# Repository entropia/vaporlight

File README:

Vaporlight
==========

The Vaporlight is Entropias LED lighting system.

More documentation (including pictures) is available
at https://entropia.de/Vaporlight.

Where to find what
------------------

/HACKING                       Describes some internals
/hardware                      Schematics and PCB layouts (Eagle)
/vaporware/led-boards          Firmware for the LED modules (C)
/config                        OpenOCD config files
/vaporware/emulator            Hardware emulator (Python)
/vaporware/daemon              TCP <-> Bus router (Scala)
/vaporware/language_bindings   Libraries for talking to the router (Python, C++)
/misc                          z.B. Schutzecken zum 3D-Drucken (OpenSCAD)

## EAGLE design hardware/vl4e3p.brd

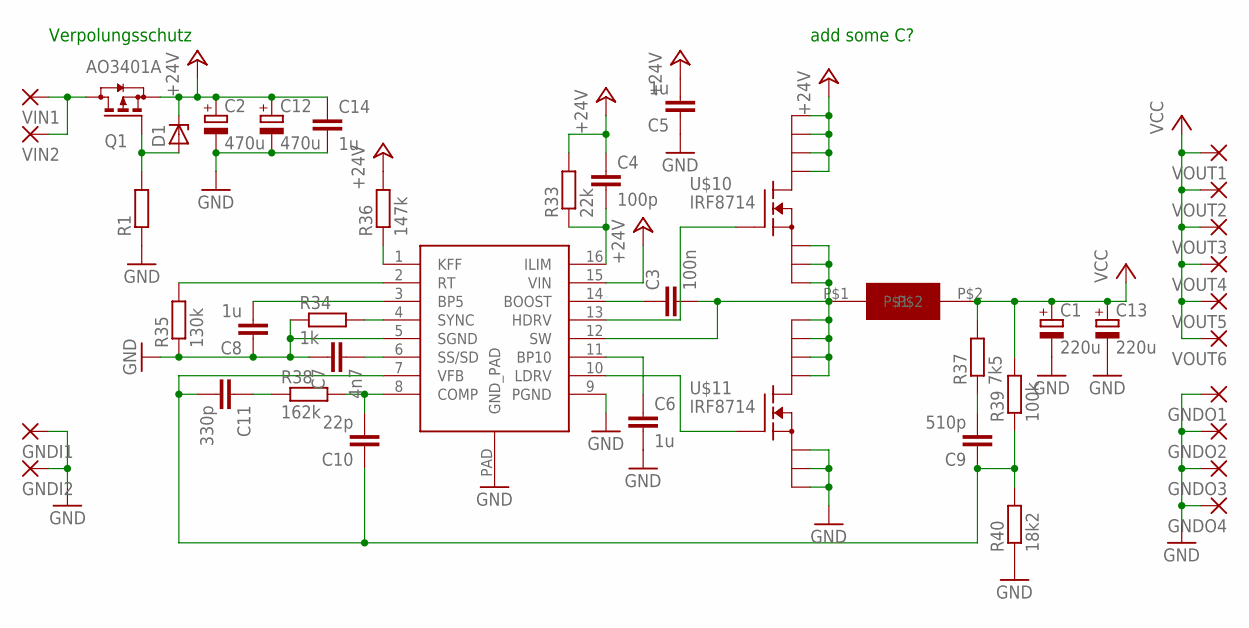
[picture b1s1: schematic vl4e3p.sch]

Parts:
C1, C13: 220u; E3,5-8
C2, C12: 470u; E3,5-8
C3: 100n; C0805S
C4: 100p; C0805
C5, C6, C8, C14: 1u; C0805
C7: 4n7; C0805
C9: 510p; C0805
C10: 22p; C0805
C11: 330p; C0805
D1: ZENER-DIODESOT23; SOT23
GNDI1, GNDI2: PAD5-2,5; 5-2,5
GNDO1, GNDO2, GNDO3, GNDO4: PAD5-2,5; 5-2,5
Q1: AO3401A; SOT23
R1: R-EU_R0805; R0805
R33: 22k; R0805
R34: 1k; R0805
R35: 130k; R0805
R36: 147k; R0805
R37: 7k5; R0805
R38: 162k; R0805
R39: 100k; R0805
R40: 18k2; R0805
U$1: 6u8; FOO
U$9: TPS40055; TSSOP16
U$10, U$11: IRF8714; SO8
VIN1, VIN2: PAD5-2,5; 5-2,5
VOUT1, VOUT2, VOUT3, VOUT4, VOUT5, VOUT6: PAD5-2,5; 5-2,5

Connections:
+24V: C2.+, C4.1, C5.2, C12.+, C14.1, D1.3 (C), Q1.2 (S), R33.2, R36.2, U$9.15 (VIN), U$10.5 (D), U$10.6 (D), U$10.7 (D), U$10.8 (D)
BOOST: C3.1, U$9.14 (BOOST)
BP10: C6.1, U$9.11 (BP10)
C3: C8.2, U$9.3 (BP5)
COMP: C10.2, R38.2, U$9.8 (COMP)
GND: C1.-, C2.-, C5.1, C6.2, C7.1, C8.1, C12.-, C13.-, C14.2, GNDI1.1, GNDI2.1, GNDO1.1, GNDO2.1, GNDO3.1, GNDO4.1, R1.1, R34.1, R35.1, R40.1, U$9.5 (SGND), U$9.9 (PGND), U$9.PAD (GND_PAD), U$11.1 (S), U$11.2 (S), U$11.3 (S)
HDRV: U$9.13 (HDRV), U$10.4 (G)
ILIM: C4.2, R33.1, U$9.16 (ILIM)
KFF: R36.1, U$9.1 (KFF)
LDRV: U$9.10 (LDRV), U$11.4 (G)
unnamed: C11.1, R38.1
unnamed: C9.2, R37.1
unnamed: D1.1 (A), Q1.1 (G), R1.2
RT: R35.2, U$9.2 (RT)
SS/SD: C7.2, U$9.6 (SS/SD)
SW: C3.2, U$1.P$1, U$9.12 (SW), U$10.1 (S), U$10.2 (S), U$10.3 (S), U$11.5 (D), U$11.6 (D), U$11.7 (D), U$11.8 (D)
SYNC: R34.2, U$9.4 (SYNC)
VCC: C1.+, C13.+, R37.2, R39.2, U$1.P$2, VOUT1.1, VOUT2.1, VOUT3.1, VOUT4.1, VOUT5.1, VOUT6.1
VFB: C9.1, C10.1, C11.2, R39.1, R40.2, U$9.7 (VFB)
VIN: Q1.3 (D), VIN1.1, VIN2.1

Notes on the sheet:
Verpolungsschutz
add some C?

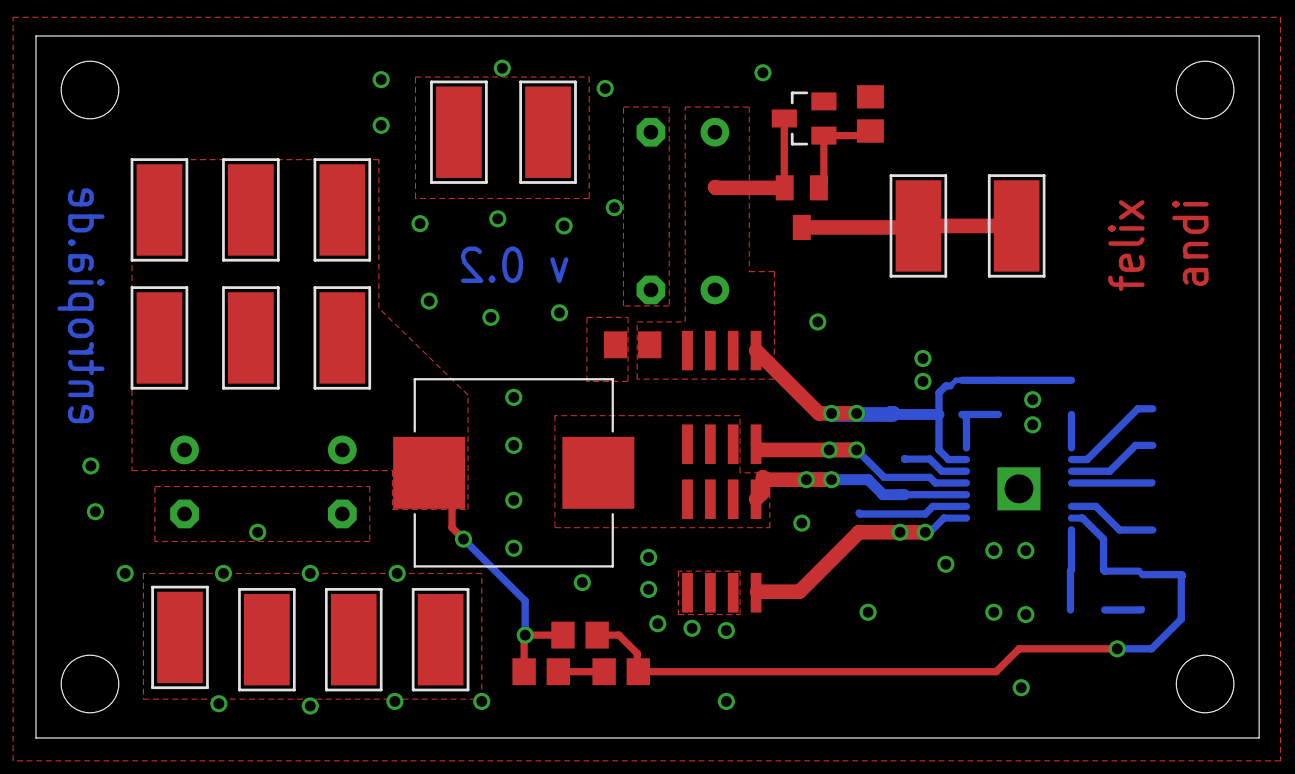
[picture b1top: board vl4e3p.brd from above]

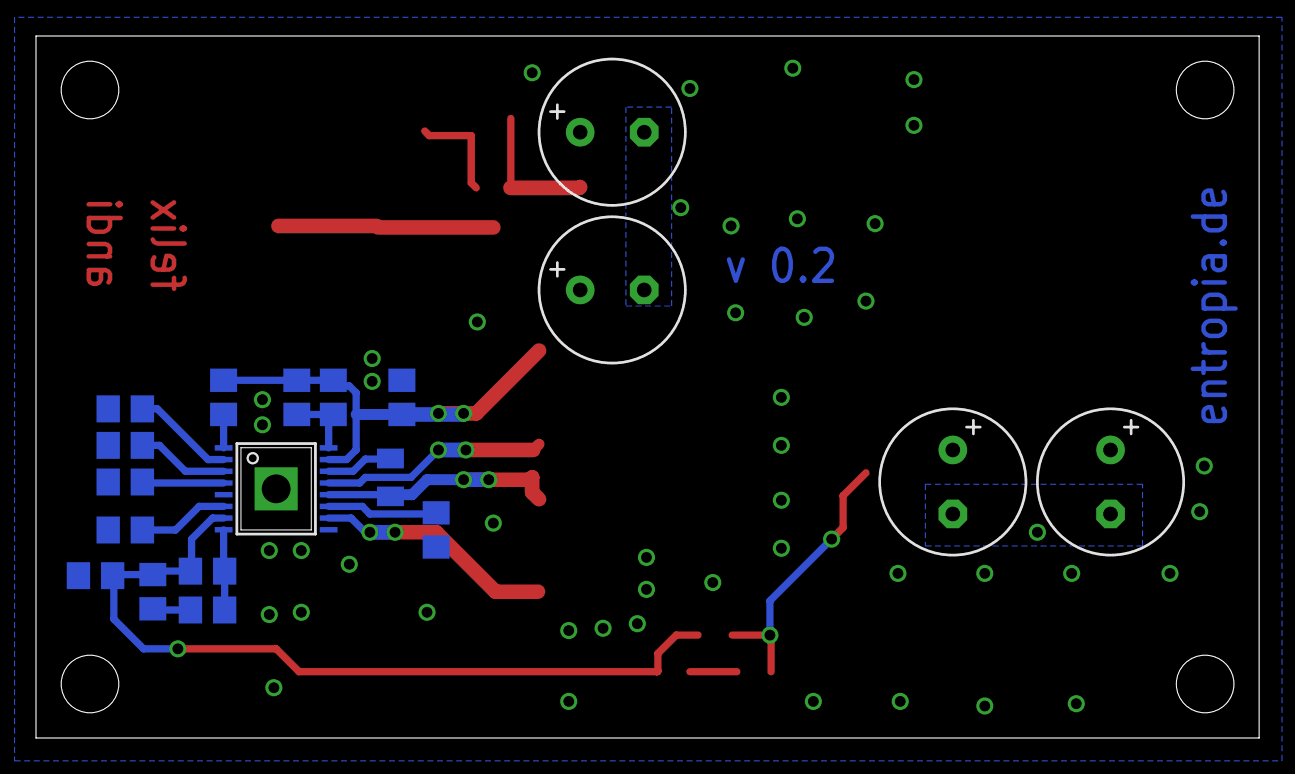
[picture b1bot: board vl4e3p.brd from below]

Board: 2 copper layers, 68.0 x 39.0 mm, 43 parts (19 on the bottom side), 20 nets.

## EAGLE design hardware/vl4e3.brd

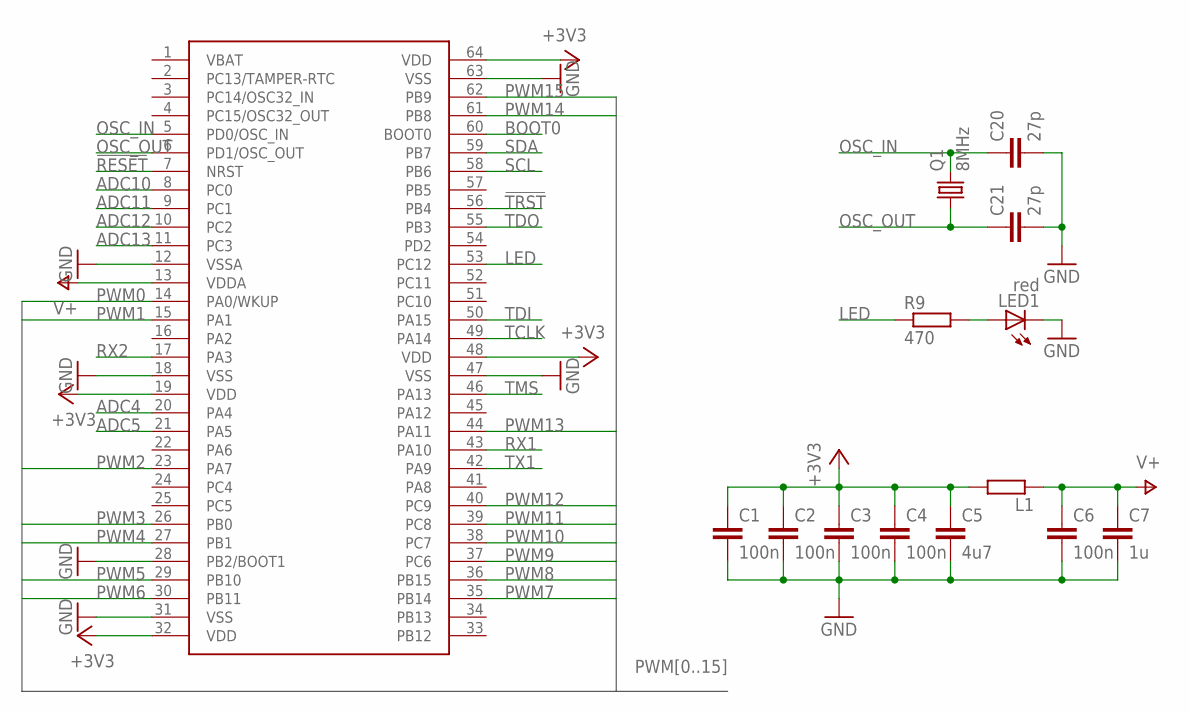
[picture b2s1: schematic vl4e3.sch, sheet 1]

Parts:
C1, C2, C3, C4, C6: 100n; C0603
C5: 4u7; C0805
C7: 1u; C0805
C20, C21: 27p; C0603
L1: R-EU_R0805; R0805
LED1: red; CHIPLED_0805
Q1: 8MHz; HC49/S
R9: 470; R0805
U$1: STM32F100R; TQFP64-10X10

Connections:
!RESET: U$1.7 (NRST); also elsewhere on the board
!TRST: U$1.56 (PB4); also elsewhere on the board
+3V3: C1.1, C2.1, C3.1, C4.1, C5.1, L1.2, U$1.19 (VDD), U$1.32 (VDD), U$1.48 (VDD), U$1.64 (VDD); also elsewhere on the board
ADC4: U$1.20 (PA4); also elsewhere on the board
ADC5: U$1.21 (PA5); also elsewhere on the board
ADC10: U$1.8 (PC0); also elsewhere on the board
ADC11: U$1.9 (PC1); also elsewhere on the board
ADC12: U$1.10 (PC2); also elsewhere on the board
ADC13: U$1.11 (PC3); also elsewhere on the board
BOOT0: U$1.60 (BOOT0); also elsewhere on the board
GND: C1.2, C2.2, C3.2, C4.2, C5.2, C6.2, C7.2, C20.2, C21.2, LED1.C, U$1.12 (VSSA), U$1.18 (VSS), U$1.28 (PB2/BOOT1), U$1.31 (VSS), U$1.47 (VSS), U$1.63 (VSS); also elsewhere on the board
LED: R9.1, U$1.53 (PC12)
LED_R: LED1.A, R9.2
OSC_IN: C20.1, Q1.2, U$1.5 (PD0/OSC_IN)
OSC_OUT: C21.1, Q1.1, U$1.6 (PD1/OSC_OUT)
PWM0: U$1.14 (PA0/WKUP); also elsewhere on the board
PWM1: U$1.15 (PA1); also elsewhere on the board
PWM2: U$1.23 (PA7); also elsewhere on the board
PWM3: U$1.26 (PB0); also elsewhere on the board
PWM4: U$1.27 (PB1); also elsewhere on the board
PWM5: U$1.29 (PB10); also elsewhere on the board
PWM6: U$1.30 (PB11); also elsewhere on the board
PWM7: U$1.35 (PB14); also elsewhere on the board
PWM8: U$1.36 (PB15); also elsewhere on the board
PWM9: U$1.37 (PC6); also elsewhere on the board
PWM10: U$1.38 (PC7); also elsewhere on the board
PWM11: U$1.39 (PC8); also elsewhere on the board
PWM12: U$1.40 (PC9); also elsewhere on the board
PWM13: U$1.44 (PA11); also elsewhere on the board
PWM14: U$1.61 (PB8); also elsewhere on the board
PWM15: U$1.62 (PB9); also elsewhere on the board
RX1: U$1.43 (PA10); also elsewhere on the board
RX2: U$1.17 (PA3); also elsewhere on the board
SCL: U$1.58 (PB6)
SDA: U$1.59 (PB7)
TCLK: U$1.49 (PA14); also elsewhere on the board
TDI: U$1.50 (PA15); also elsewhere on the board
TDO: U$1.55 (PB3); also elsewhere on the board
TMS: U$1.46 (PA13); also elsewhere on the board
TX1: U$1.42 (PA9); also elsewhere on the board
V+: C6.1, C7.1, L1.1, U$1.13 (VDDA)

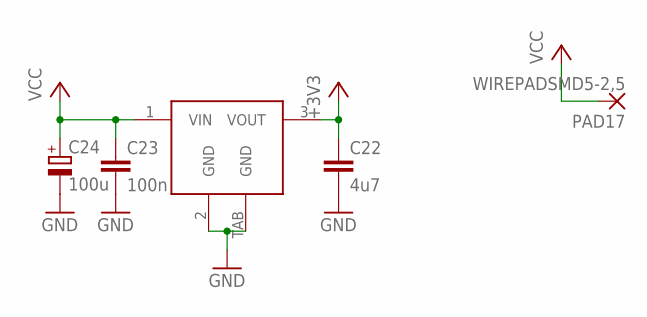
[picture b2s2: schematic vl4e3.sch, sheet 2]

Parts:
C22: 4u7; C0805
C23: 100n; C0603
C24: 100u; E2,5-6
PAD17: WIREPADSMD5-2,5; 5-2,5
U$10: MIC5209; SOT223

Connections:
+3V3: C22.1, U$10.3 (VOUT); also elsewhere on the board
GND: C22.2, C23.2, C24.-, U$10.2 (GND), U$10.TAB (GND); also elsewhere on the board
VCC: C23.1, C24.+, PAD17.1, U$10.1 (VIN); also elsewhere on the board

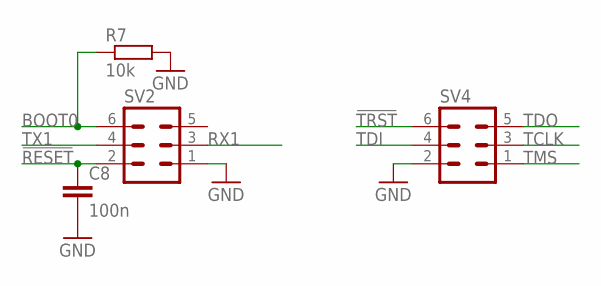
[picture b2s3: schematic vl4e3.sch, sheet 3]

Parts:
C8: 100n; C0603
R7: 10k; R0603
SV2, SV4: MA03-2

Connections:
!RESET: C8.1, SV2.2; also elsewhere on the board
!TRST: SV4.6; also elsewhere on the board
BOOT0: R7.1, SV2.6; also elsewhere on the board
GND: C8.2, R7.2, SV2.1, SV4.2; also elsewhere on the board
RX1: SV2.3; also elsewhere on the board
TCLK: SV4.3; also elsewhere on the board
TDI: SV4.4; also elsewhere on the board
TDO: SV4.5; also elsewhere on the board
TMS: SV4.1; also elsewhere on the board
TX1: SV2.4; also elsewhere on the board

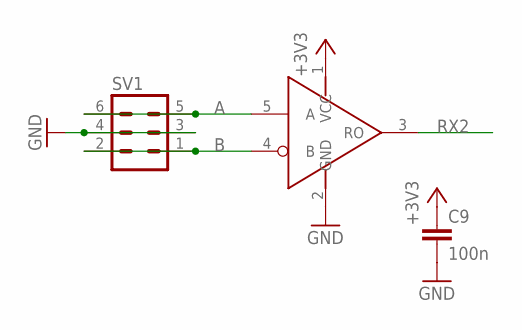
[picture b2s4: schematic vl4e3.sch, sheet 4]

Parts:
C9: 100n; C0603
SV1: MA03-2
U$13: ISL3280E; SOT23-5L

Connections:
+3V3: C9.1, U$13.1 (VCC); also elsewhere on the board
A: SV1.5, SV1.6, U$13.5 (A)
B: SV1.1, SV1.2, U$13.4 (B)
GND: C9.2, SV1.3, SV1.4, U$13.2 (GND); also elsewhere on the board
RX2: U$13.3 (RO); also elsewhere on the board

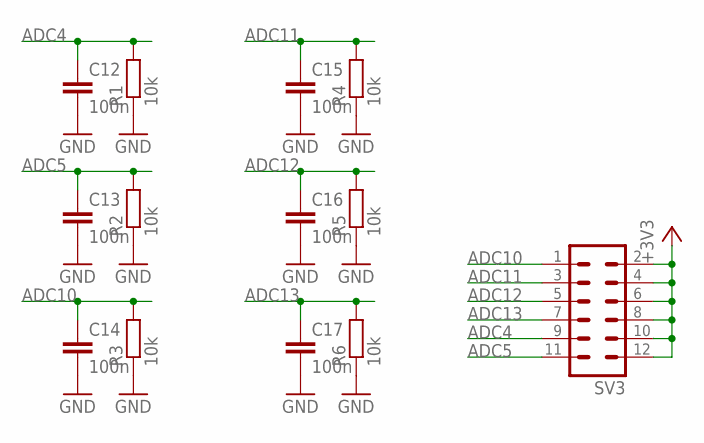
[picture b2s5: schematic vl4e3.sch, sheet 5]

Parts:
C12, C13, C14, C15, C16, C17: 100n; C0603
R1, R2, R3, R4, R5, R6: 10k; R0603
SV3: MA06-2

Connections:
+3V3: SV3.2, SV3.4, SV3.6, SV3.8, SV3.10, SV3.12; also elsewhere on the board
ADC4: C12.1, R1.2, SV3.9; also elsewhere on the board
ADC5: C13.1, R2.2, SV3.11; also elsewhere on the board
ADC10: C14.1, R3.2, SV3.1; also elsewhere on the board
ADC11: C15.1, R4.2, SV3.3; also elsewhere on the board
ADC12: C16.1, R5.2, SV3.5; also elsewhere on the board
ADC13: C17.1, R6.2, SV3.7; also elsewhere on the board
GND: C12.2, C13.2, C14.2, C15.2, C16.2, C17.2, R1.1, R2.1, R3.1, R4.1, R5.1, R6.1; also elsewhere on the board

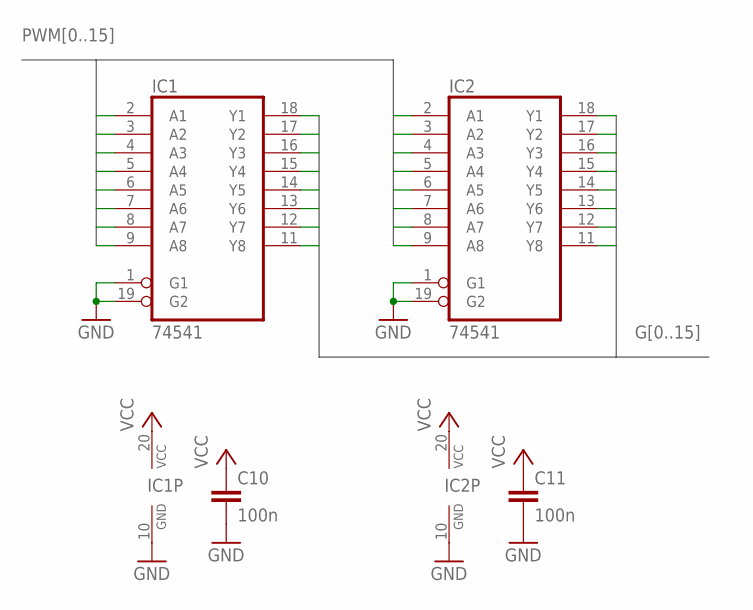
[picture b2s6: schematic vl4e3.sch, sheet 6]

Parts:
C10, C11: 100n; C0603
IC1, IC2: 74541; TSSOP20

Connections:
G0: IC1.18 (Y1); also elsewhere on the board
G1: IC1.17 (Y2); also elsewhere on the board
G2: IC1.16 (Y3); also elsewhere on the board
G3: IC1.15 (Y4); also elsewhere on the board
G4: IC1.14 (Y5); also elsewhere on the board
G5: IC1.13 (Y6); also elsewhere on the board
G6: IC1.12 (Y7); also elsewhere on the board
G7: IC1.11 (Y8); also elsewhere on the board
G8: IC2.18 (Y1); also elsewhere on the board
G9: IC2.17 (Y2); also elsewhere on the board
G10: IC2.16 (Y3); also elsewhere on the board
G11: IC2.15 (Y4); also elsewhere on the board
G12: IC2.14 (Y5); also elsewhere on the board
G13: IC2.13 (Y6); also elsewhere on the board
G14: IC2.12 (Y7); also elsewhere on the board
G15: IC2.11 (Y8); also elsewhere on the board
GND: C10.2, C11.2, IC1.1 (G1), IC1.10 (GND), IC1.19 (G2), IC2.1 (G1), IC2.10 (GND), IC2.19 (G2); also elsewhere on the board
PWM0: IC1.2 (A1); also elsewhere on the board
PWM1: IC1.3 (A2); also elsewhere on the board
PWM2: IC1.4 (A3); also elsewhere on the board
PWM3: IC1.5 (A4); also elsewhere on the board
PWM4: IC1.6 (A5); also elsewhere on the board
PWM5: IC1.7 (A6); also elsewhere on the board
PWM6: IC1.8 (A7); also elsewhere on the board
PWM7: IC1.9 (A8); also elsewhere on the board
PWM8: IC2.2 (A1); also elsewhere on the board
PWM9: IC2.3 (A2); also elsewhere on the board
PWM10: IC2.4 (A3); also elsewhere on the board
PWM11: IC2.5 (A4); also elsewhere on the board
PWM12: IC2.6 (A5); also elsewhere on the board
PWM13: IC2.7 (A6); also elsewhere on the board
PWM14: IC2.8 (A7); also elsewhere on the board
PWM15: IC2.9 (A8); also elsewhere on the board
VCC: C10.1, C11.1, IC1.20 (VCC), IC2.20 (VCC); also elsewhere on the board

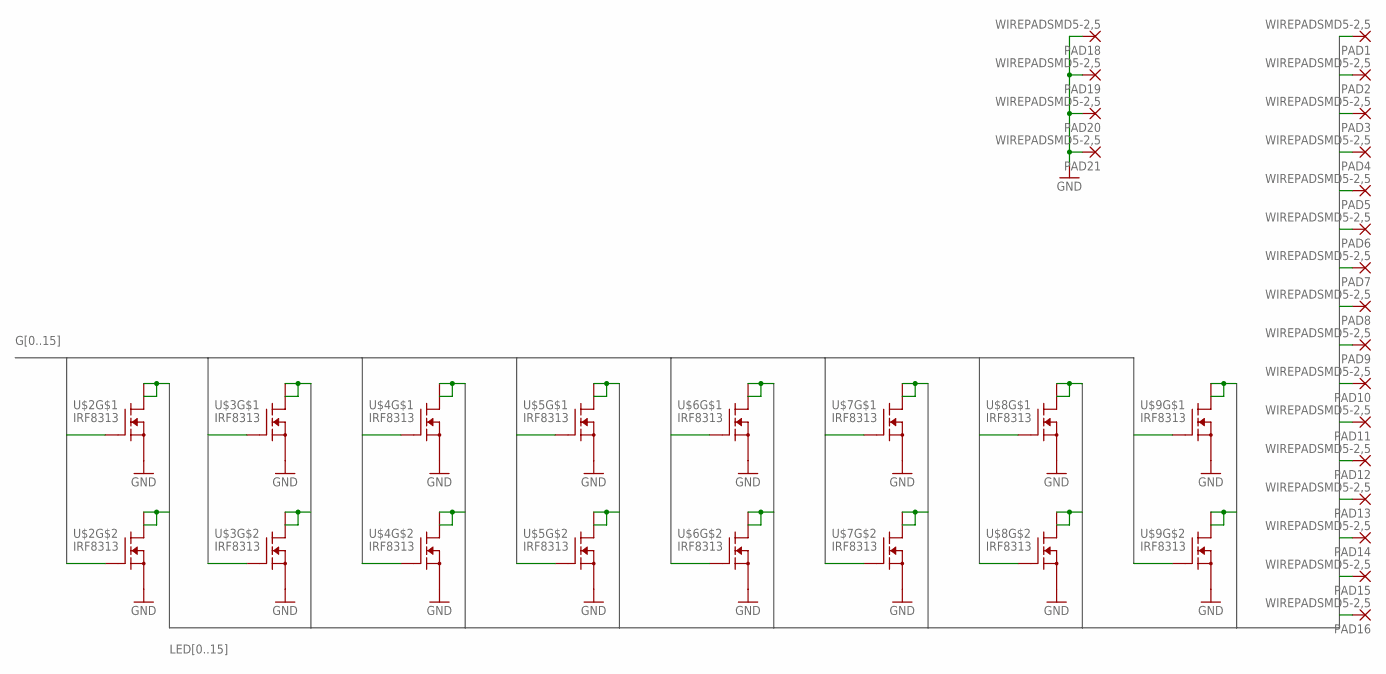
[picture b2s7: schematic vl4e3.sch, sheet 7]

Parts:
PAD1, PAD2, PAD3, PAD4, PAD5, PAD6, PAD7, PAD8, PAD9, PAD10, PAD11, PAD12, PAD13, PAD14, PAD15, PAD16, PAD18, PAD19, PAD20, PAD21: WIREPADSMD5-2,5; 5-2,5
U$2, U$3, U$4, U$5, U$6, U$7, U$8, U$9: IRF8313; SO-08

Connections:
G0: U$2.2 (G); also elsewhere on the board
G1: U$2.4 (G); also elsewhere on the board
G2: U$3.2 (G); also elsewhere on the board
G3: U$3.4 (G); also elsewhere on the board
G4: U$4.2 (G); also elsewhere on the board
G5: U$4.4 (G); also elsewhere on the board
G6: U$5.2 (G); also elsewhere on the board
G7: U$5.4 (G); also elsewhere on the board
G8: U$6.2 (G); also elsewhere on the board
G9: U$6.4 (G); also elsewhere on the board
G10: U$7.2 (G); also elsewhere on the board
G11: U$7.4 (G); also elsewhere on the board
G12: U$8.2 (G); also elsewhere on the board
G13: U$8.4 (G); also elsewhere on the board
G14: U$9.2 (G); also elsewhere on the board
G15: U$9.4 (G); also elsewhere on the board
GND: PAD18.1, PAD19.1, PAD20.1, PAD21.1, U$2.1 (S), U$2.3 (S), U$3.1 (S), U$3.3 (S), U$4.1 (S), U$4.3 (S), U$5.1 (S), U$5.3 (S), U$6.1 (S), U$6.3 (S), U$7.1 (S), U$7.3 (S), U$8.1 (S), U$8.3 (S), U$9.1 (S), U$9.3 (S); also elsewhere on the board
LED0: PAD1.1, U$2.7 (D), U$2.8 (D)
LED1: PAD2.1, U$2.5 (D), U$2.6 (D)
LED2: PAD3.1, U$3.7 (D), U$3.8 (D)
LED3: PAD4.1, U$3.5 (D), U$3.6 (D)
LED4: PAD5.1, U$4.7 (D), U$4.8 (D)
LED5: PAD6.1, U$4.5 (D), U$4.6 (D)
LED6: PAD7.1, U$5.7 (D), U$5.8 (D)
LED7: PAD8.1, U$5.5 (D), U$5.6 (D)
LED8: PAD9.1, U$6.7 (D), U$6.8 (D)
LED9: PAD10.1, U$6.5 (D), U$6.6 (D)
LED10: PAD11.1, U$7.7 (D), U$7.8 (D)
LED11: PAD12.1, U$7.5 (D), U$7.6 (D)
LED12: PAD13.1, U$8.7 (D), U$8.8 (D)
LED13: PAD14.1, U$8.5 (D), U$8.6 (D)
LED14: PAD15.1, U$9.7 (D), U$9.8 (D)
LED15: PAD16.1, U$9.5 (D), U$9.6 (D)

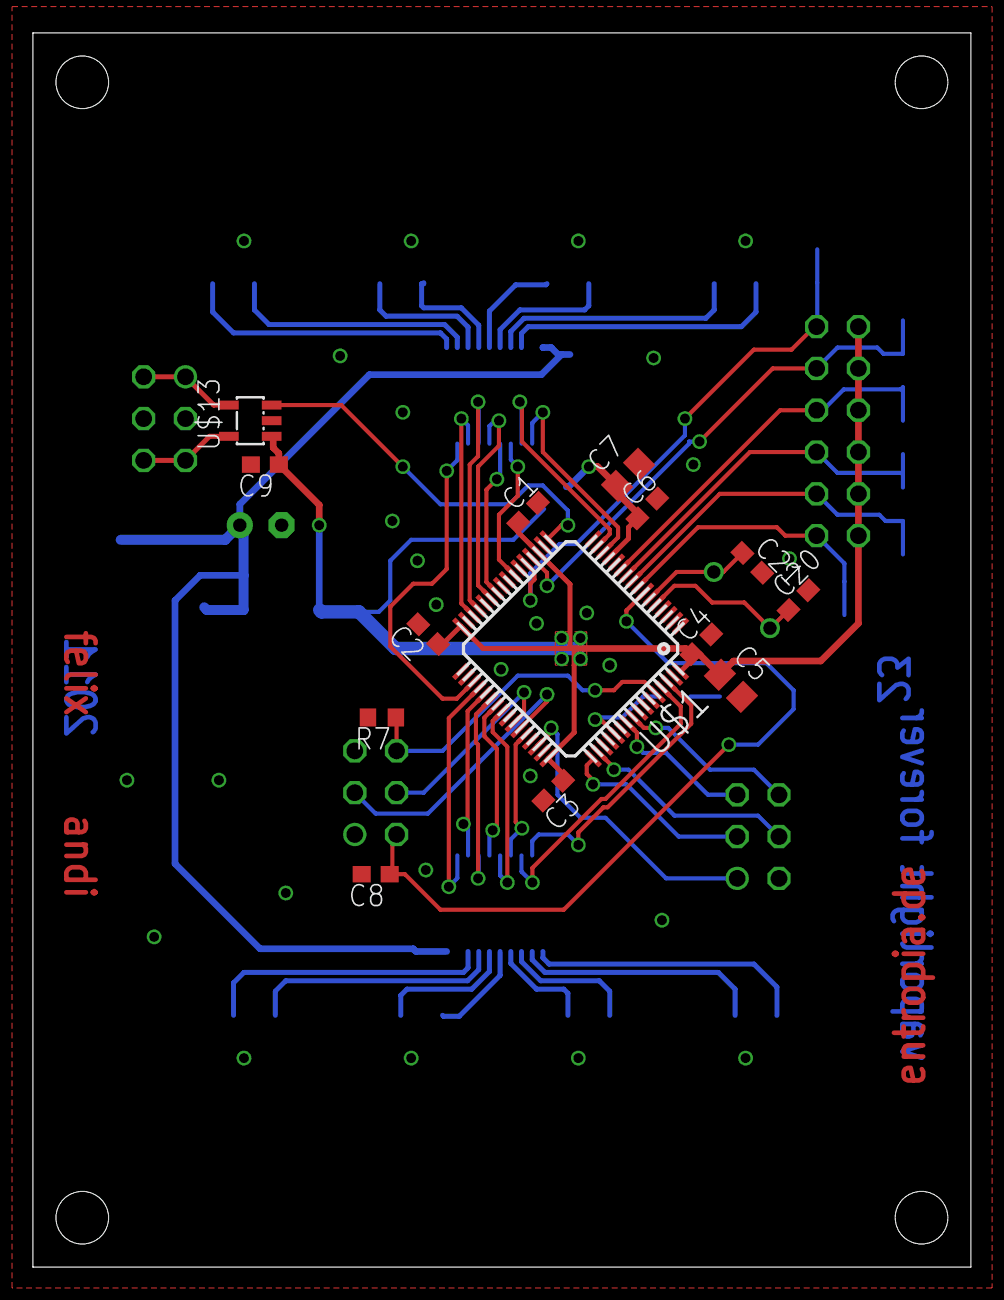
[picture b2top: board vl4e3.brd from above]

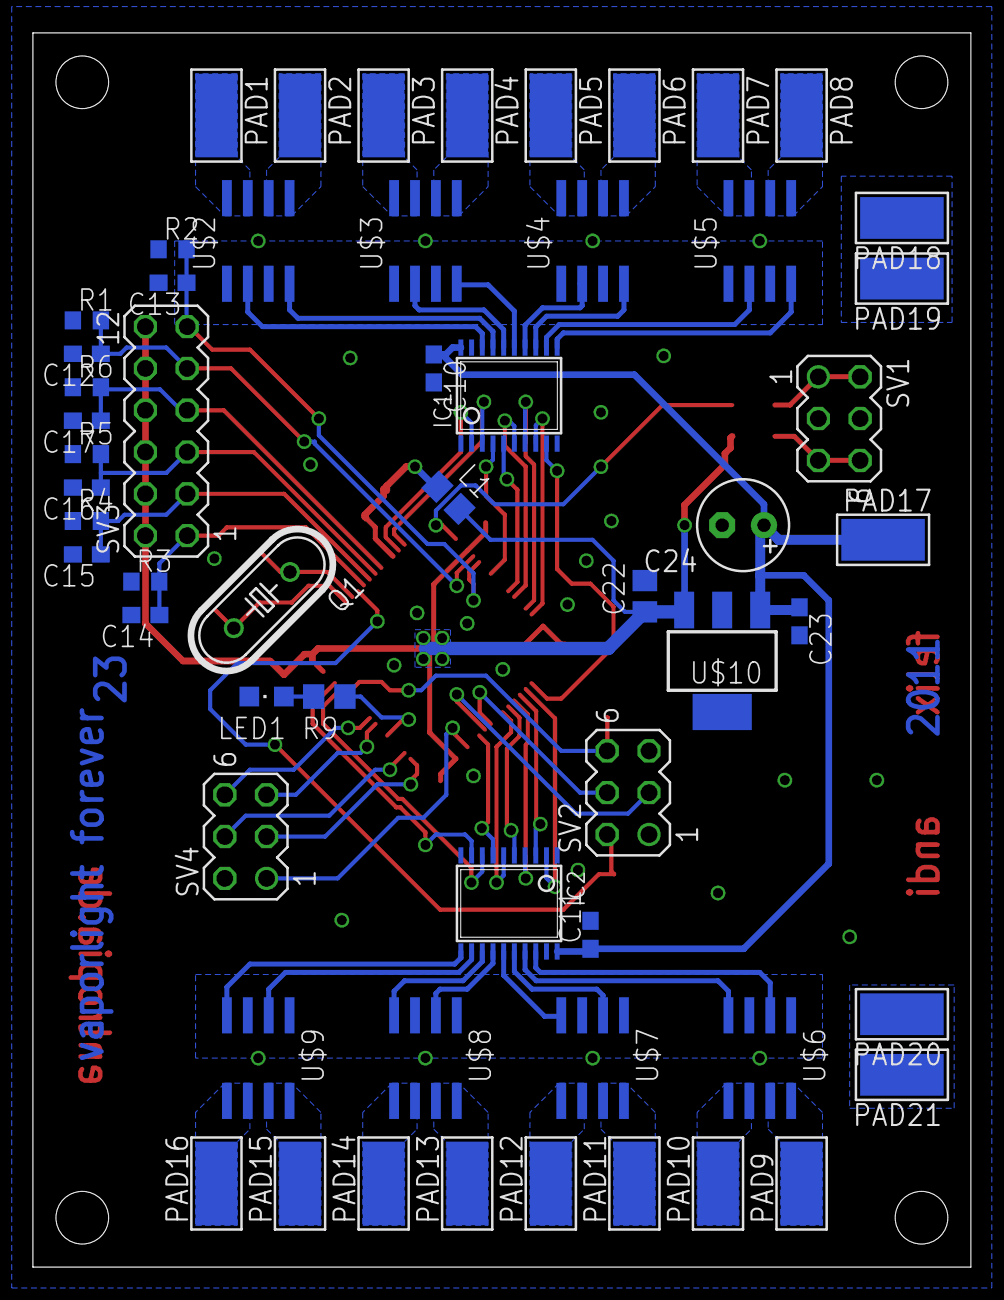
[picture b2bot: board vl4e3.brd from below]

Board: 2 copper layers, 57.0 x 75.0 mm, 71 parts (57 on the bottom side), 74 nets.

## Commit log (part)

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2012-09-28 Initial public commit.
2012-09-28 Added first hardware designs (by @felixheld).
    This contains the controller board for the LED modules and the step-down
    converter for the LEDs.
2012-09-28 Upgrade vl4e3 to EAGLE 6.0 file format
    Upgrade the file format of the control board
    to the plain-text EAGLE 6.0 format.
2012-10-17 add configuration for OpenOCD
    This adds a customized version of the OpenOCD stm32f1x target with a
    lower WORKAREASIZE to account for the lower amount of available memory
    on the Vaporlight boards.
2012-12-01 added c++-language-bindings
2012-12-01 updated .gitignore
2012-12-01 Second public release of the firmware.
    Major changes:
    - Gamma table can be read and updated at runtime.
    - Low-level improvements to the console: It is now interrupt-driven and
    uses flow control. This makes it possible to paste configuration files
    into the console without losing data.
2012-12-01 made build configurable and improved the fade-implementation
2012-12-02 improved the client-class and the fade-implementation
2012-12-02 added buffer-access for inherited classes and virtual destructor for vlpp::client
2012-12-07 added torture-device and made pimpl less painfull
2012-12-08 replaced manual locking by lock-guard
2012-12-09 several changes
2013-01-19 several improvements
2013-01-19 removed old files
2013-01-19 improved blinker and utility-lib
2013-01-19 restructured blinker
2013-01-21 fixed rvalue-moves
2013-01-21 added nicer termination for blinker (SIGINT)
2013-01-23 Add python bindings
2013-01-23 Add rainbow animation
2013-01-23 Improve python3 compatibility
2013-03-21 (Yet another) Initial commit
2013-03-21 Add .gitignore
2013-03-29 Add an emulator (that speaks the bus protocol)
2013-03-30 Emulator: Bugfix: sample file was missing strobe command
2013-03-30 Emulator can now use stdin instead of sockets
2013-03-30 Emulator: Bugfix: wait for strobe commands
2013-03-30 Emulator: Bugfix: don't silence exceptions
2013-03-30 Emulator: Bugfix: detect closed connections properly
2013-03-31 Emulator: bugfix: strobe is 0xfe not 0xff, oops
2013-03-31 Emulator: debug output: print received frames
2013-03-31 Import
2013-04-01 Emulator: refactoring + comments
2013-04-15 Emulator: bugfix: use GObject.idle_add
    Redrawing should now work properly with fast updates too.
2013-04-15 Read settings from a config file
    We use Typesafes config library for this;
    it seems slightly less annoying than the alternatives.
2013-04-15 Remove some log statements
2013-04-16 Bugfix: double strobe
    This is a workaround for a problem with the bus protocol:
    Because of how framing works, the Vaporlight firmware currently
    only detects the end of a frame by waiting for the beginning of
    the next frame. This is problematic if only a single strobe
    without further messages is sent.
2013-04-17 Bugfix: for when only some LEDs of a module are updated
2013-04-17 Add a test
2013-04-17 Add lost connection handling
    When a client disconnects, its overlay is removed from the mixer
    and the LEDs are updated accordingly.
    Individual tokens can be marked as persistent. The overlays
    for these tokens are kept even when the connection is closed.
2013-04-20 Ignore invalid set-led
    Don't throw when theres no mapping for a LED
2013-04-24 Autoformat
2013-04-26 Add README.rst, AUTHORS, LICENSE
2013-04-26 Oops, the actual LED modules have 16 leds
2013-04-26 Add "file" device type
    Somewhat useful for debugging; this way one can use a hex editor
    to check what the router would send to the hardware
2013-04-26 Add logback.xml
2013-04-26 Use debug() instead of info() where it makes sense
2013-04-30 Very simple fading animation
2013-04-30 Add latency test script
    I used this to get a rough idea what the latency
    of the scala daemon is
2013-04-30 Very simple RGB lauflicht script
2013-04-30 Add a smooth lauflicht effect
2013-05-12 Add __version__ to llvp.py
2013-06-09 Small bugfix for one of the demo programs
2013-07-21 Use typesafes scalalogging instead of grizzled
2013-07-21 Bugfix: wrong type conversion in settings parser
    Wrong::
    scala> "243".toByte
    java.lang.NumberFormatException: Value out of range. Value:"243" Radix:10
    Right::
    scala> "243".toInt.toByte
    res2: Byte = -13
2013-07-22 Daemon: Make baudrate configurable
2013-07-22 Add logging config file
2013-07-22 Daemon: listen on all interfaces by default
2013-07-23 Daemon: Add "Configuration" section to README
2013-07-23 Fix openocd config
2013-07-23 Add openocd config file for our JTAG adapter
2013-07-23 Daemon: document config files
2013-07-23 Add flash script
2013-07-23 Python script cleanup
    Use command line options to pass connection
    data instead of a login.py
2013-07-23 Firmware: add BUS_BAUDRATE parameter
2013-08-20 Remove unneeded files.
    macros.h was only relevant to the AVR version.
    usart.c has been replaced by usart1.c and usart2.c.
2013-08-22 Add a check for invalid baud rates.
    To support more baud rates, add to the #if-#else-cascade.
2013-09-07 Ignore etags TAGS file.
2013-09-18 Fix console system reset command.
2013-09-22 Daemon: don't double strobe
    Turns out double strobe is not actually necessary (anymore?)
2013-09-22 Daemon: Add sbt-onejar to project/plugins
2013-09-22 Daemon: set version to 0.1.0-SNAPSHOT
2013-09-22 Remove whitepoint correction setting (to be replaced by calibration).
2013-09-22 Implemented console functions to set up correction and maximum Y value.
2013-09-22 Change pwm_set_brightness to take 16-bit values.
2013-09-22 Implemented color calibration. Compiler change was necessary.
2013-09-22 Remove gamma table.
2013-09-22 Remove LED permutation config, fix flash config page.
2013-09-22 Move module "led" to "pwm".
2013-09-22 Refactoring: Introduce RGB_LED_COUNT, clear distinction LED <-> PWM channel.
2013-09-22 Add convert_channel_index.
2013-09-22 Store backup channel in config.
2013-09-22 Remove whitepoint calibration mode.
2013-09-22 Fix color_correct: Adjust color first, then luminosity.
2013-09-22 remove console_wp module from OBJ list.
2013-09-22 Implemented new 16-bit "set LEDs" command.
2013-09-22 add -Wextra flag.
2013-09-22 Signedness corrections.
2013-09-22 Add config check for valid PWM channel assignment.
2013-09-22 Remove all pointers to led_info_t.
    Pointing to a packed struct is undefined.
2013-09-22 Documentation & whitespace.
2013-09-22 Split console_int into console_uint and console_sint. Add console_fixed.
2013-09-22 Fix linker script (take care of the .ARM.exidx section).
2013-09-22 Implement fixed-point arithmetic and replace all float operations.
2013-09-22 Panic in fixdiv when dividing by zero.
2013-09-22 Convert channel index in set_brightness.
2013-09-22 Shorten console messages.
2013-09-22 Add LED calibration command.
2013-09-22 Remove double invalid configuration error message.
2013-09-22 Add and use console_ask_int.
2013-09-22 Remove the call to strncmp (dramatically reduces the code size).
2013-09-22 Improve command tracing.
    Note that tracing is now more verbose and should not be used under load.
2013-09-24 Add HACKING, move protocol description there
2013-09-24 Daemon: use new bus protocol
    This is just a quick fix; we don't make use of the
    new features yet:
    - we set raw pwm values instead of xyY colors
    - we use only 8 bit precision instead of 16
2013-09-24 Document new bus protocol
2013-09-27 Document the new 16-bit set-led command
2013-09-27 Daemon: use 16 bit precision Colors internally
2013-09-27 Daemon: add HighPrecisionSetMessage
    This makes it possible to specify colors using 16-bit precision.
    Opcode 0x03, payload bytes: mlRrGgBbAa (m: module, l: led).
2013-09-27 Daemon: rename SetMessage to LowPrecisionSetMessage
2013-09-27 Add some comments
2013-09-27 Set python binding version to 0.3.0
2013-09-29 Daemon: bugfix
    After parsing a HighPrecisionSetMessage, the daemon would create
    a LowPrecisionSetMessage object instead. This didn't have any
    consequences though, because the Color was parsed correctly.
2013-09-29 Make 'fade.py' use high resolution commands
2013-09-29 Daemon: Bugfix for layer ordering
    We never actually sorted the layers because the sorting
    function we called didn't sort in-place but returned a new
    container, which we discarded. Oops.
2013-09-29 Daemon: add web server
    It offers a simple API that can currently be used
    to control a global dimmer and a backlight.
    It will always listen on 0.0.0.0:8080
2013-09-29 Daemon: make server interface/port configurable
2013-09-30 Document /api/clients
2013-11-10 Minor protocol changes + daemon implementation
2013-11-10 Implement the new RS485 bus protocol in the LED board firmware.
    See also HACKING.
2013-12-10 Daemon: update build.sbt
2013-12-10 Daemon: add docs link to webinterface
2014-01-13 router: fix tests
    They were broken due to the high-precision color changes.
2014-01-13 Move constant
2014-01-13 Daemon: 16 bit precision for dimmer
2014-01-13 Daemon: document default port for http api
2014-01-13 Daemon: set version to 0.1.1
2014-01-14 Daemon: support jsonp
2014-01-14 HACKING: document jsonp
2014-01-14 Daemon: version 0.1.2
2014-01-14 Daemon: back to -SNAPSHOT
2014-01-14 Daemon: allow same-origin policy bypass
    *duck*
2014-02-15 Daemon: webhook support
2014-02-15 Documentation
2014-02-17 Fix a desynchronisation bug.
    When a start byte was received during a frame, the message that was being
    assembled at the time was not correctly cleaned up.
2014-02-17 firmware: colorfully display the firmware version during boot
2014-02-17 firmware: actually update pwm state in display_version()
2014-02-17 util: version-color.py
2014-02-17 firmware: display something during boot even without a channel mapping
2014-02-17 util: update version-color.py to match the new color output
2014-02-19 Firmware: Fix escaping bugs.
    This should correct the cases where a module would hang up in the middle
    of an animation.
2014-02-19 Firmware: Do not blink a debug code for transient failures.
2014-02-19 Firmware: Do not export the .config section into the image files.
2014-02-19 Firmware: Output mode information when a bogus USART command is received.
2014-03-03 Daemon: Support jsonp for /api/clients
    Quick fix; I'll have to clean this up later.
2014-03-03 Daemon: /api/clients: return clients as array
    Easier to handle in JavaScript than one-result-per-line.
2014-05-11 Firmware: Update OpenOCD interface script to work with openocd 0.8.0.
2014-07-20 Fix rainbow demo script
2014-07-21 Daemon: update purejavacomm entry in build.sbt to 0.20
    v0.20 fixes https://github.com/nyholku/purejavacomm/issues/43
2014-10-13 Corner protection guards
    The vaporlight case corners are quite sharp.
2014-11-14 Adds go language binding
2014-11-14 Language bindings: Adds another python example
2014-11-16 Language bindings: gofmt'd the go bindings and example
2015-02-03 Daemon: remove SCCT. It broke the build.
2015-06-21 hardware: update stepdown schematic to eagle 6.5
2015-06-21 hardware: increase current limit of stepdown
    The old resistor value was based on a very tightly calculated current
    limit and was also rounded down to match an E12 value. This caused some
    aging Vaporlights to fail when drawing more current (e.g. displaying all
    white).
2015-09-14 added Java bindings for vaporlight and bubblesort
2016-01-26 Add in-system firmware updater.
    Due to lack of Flash space, in-system calibration has been removed.
2016-04-15 Add alternative python implementation
2016-04-15 Add pyVaporlight/README.md
2016-06-05 HACKING: fix network protocol spec
2016-06-06 HACKING: fix network protocol spec (#11)
    HACKING: fix network protocol spec
2016-10-08 Language bindings: 16 bit commands in go bindings
2016-10-21 Language bindings (+example) for rust.
    The vaporlight package can also be found on crates.io
2016-10-21 Language bindings: rust example now with crates.io dep
    The vaporlight package is now built from crates.io for the rainbow
    example
2017-01-10 Add Node.js language bindings
2017-01-10 Add comments
